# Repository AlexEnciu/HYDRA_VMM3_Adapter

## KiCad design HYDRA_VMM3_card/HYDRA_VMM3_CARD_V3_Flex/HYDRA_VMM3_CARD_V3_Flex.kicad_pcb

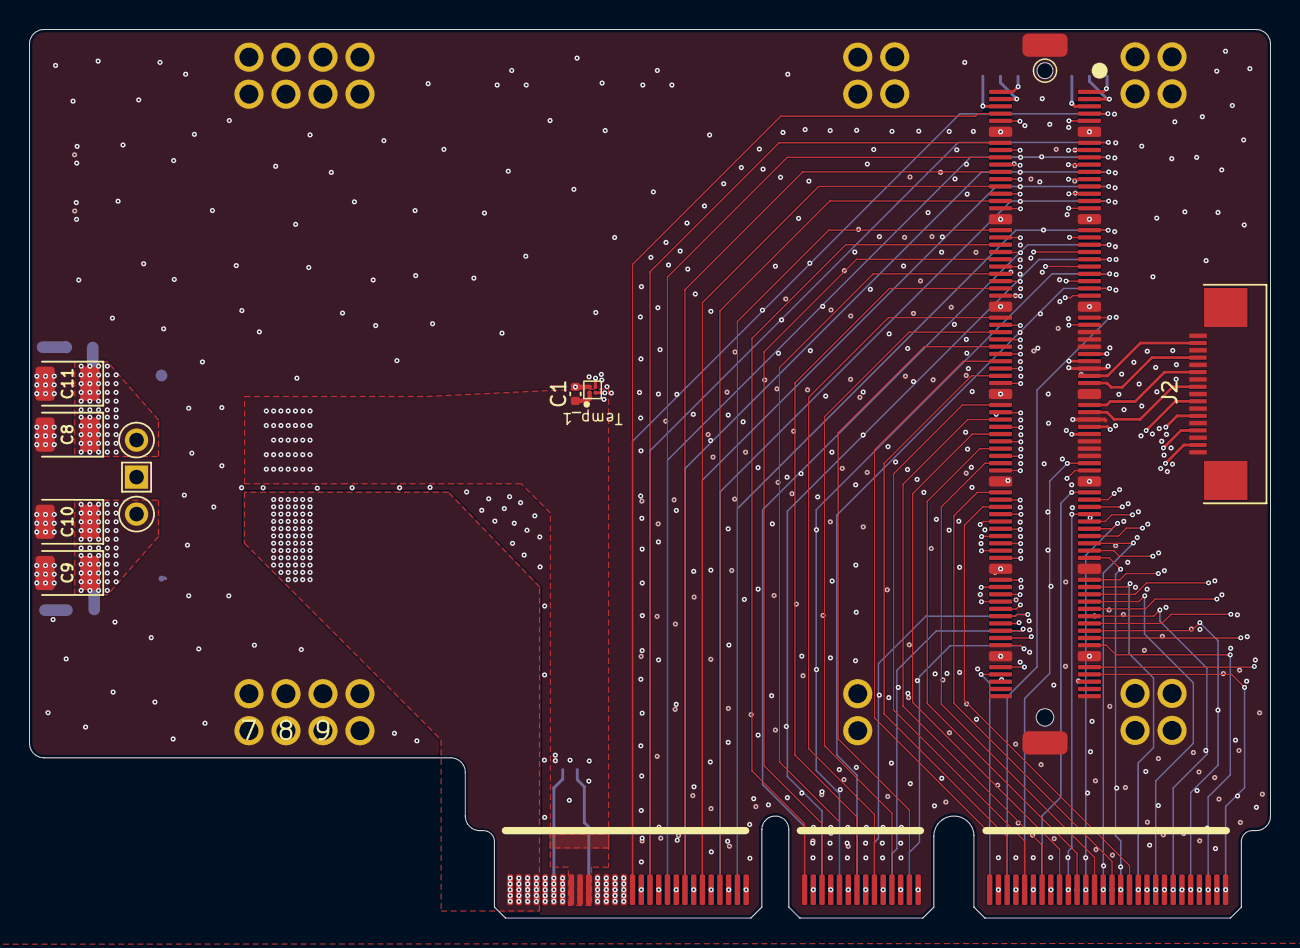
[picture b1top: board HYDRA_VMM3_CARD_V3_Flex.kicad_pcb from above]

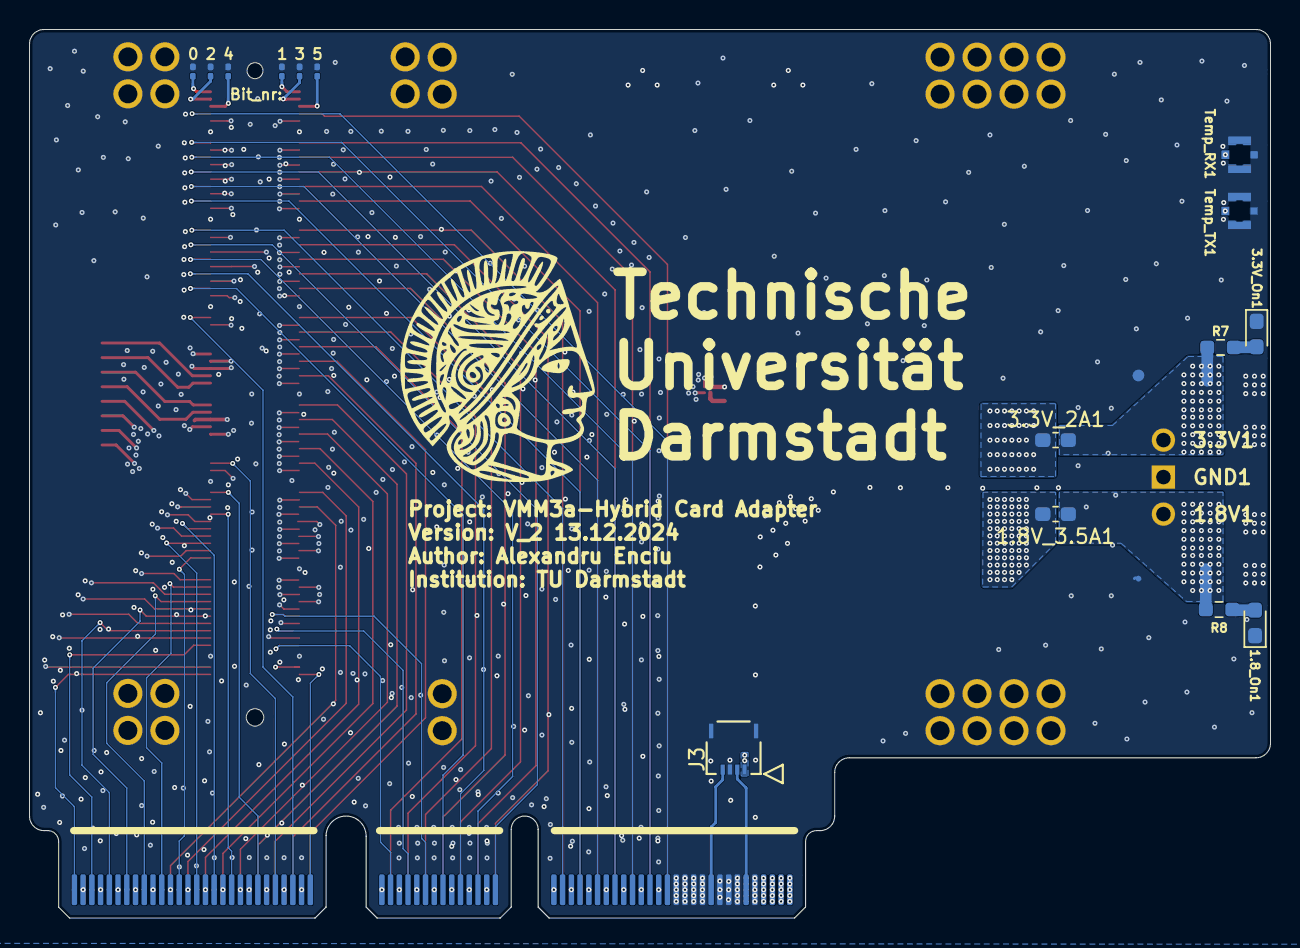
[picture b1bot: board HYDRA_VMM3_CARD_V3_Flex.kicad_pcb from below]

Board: 8 copper layers, 85.2 x 61.0 mm, 43 parts (15 on the bottom side), 136 nets.

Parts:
1, 2, 4, 5, 7, 8, 9, 11, 12, 13, 14, 15, 17, 20, 23, 24: (no value)
1.8V1: 1.8V; TestPoint_Pad_D2.5mm
1.8V_3.5A1: 2.5A; Fuse_0603_1608Metric_Pad1.05x0.95mm_HandSolder
1.8_On1, 3.3V_On1: LED; LED_0603_1608Metric_Pad1.05x0.95mm_HandSolder
3.3V1: 3.3V; TestPoint_Pad_D2.5mm
3.3V_2A1: 2A; Fuse_0603_1608Metric_Pad1.05x0.95mm_HandSolder
C1: 100nF; C_0402_1005Metric
C8, C9, C10, C11: TCJB475M025R0100; CP_EIA-3528-12_Kemet-T
GND1: GND; TestPoint_Pad_2.5x2.5mm
J1: ME1014010101011; Edge-Card-Connector
J2: FPC: 68711714522; 68711714522
J3: FPC_4pin; CON_5034800440_MOL
R1, R2, R3, R4, R5, R6: 10k; R_0201_0603Metric
R7, R8: 1k; R_0603_1608Metric_Pad0.98x0.95mm_HandSolder
Temp_1: TMP104
Temp_RX1: 20449-001E-03; IPEX_20449-001E-03
Temp_TX1: 20449-001E-03; IPEX_20449-001E-03
U1: Hirose-FX10

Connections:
Ch_0: J1.B15, U1.8
Ch_1: J1.A15, U1.7
Ch_2: J1.B16, U1.10
Ch_3: J1.A16, U1.9
Ch_4: J1.B17, U1.12
Ch_5: J1.A17, U1.11
Ch_6: J1.B18, U1.14
Ch_7: J1.A18, U1.13
Ch_8: J1.B19, U1.16
Ch_9: J1.A19, U1.15
Ch_10: J1.B20, U1.18
Ch_11: J1.A20, U1.17
Ch_12: J1.B21, U1.20
Ch_13: J1.A21, U1.19
Ch_14: J1.B22, U1.22
Ch_15: J1.A22, U1.21
Ch_16: J1.B23, U1.24
Ch_17: J1.A23, U1.23
Ch_18: J1.B24, U1.26
Ch_19: J1.A24, U1.25
Ch_20: J1.B25, U1.28
Ch_21: J1.A25, U1.27
Ch_22: J1.B26, U1.30
Ch_23: J1.A26, U1.29
Ch_24: J1.B27, U1.32
Ch_25: J1.A27, U1.31
Ch_26: J1.B28, U1.34
Ch_27: J1.A28, U1.33
Ch_28: J1.B29, U1.36
Ch_29: J1.A29, U1.35
Ch_30: J1.B30, U1.38
Ch_31: J1.A30, U1.37
Ch_32: J1.B31, U1.40
Ch_33: J1.A31, U1.39
Ch_34: J1.B32, U1.42
Ch_35: J1.A32, U1.41
Ch_36: J1.B33, U1.44
Ch_37: J1.A33, U1.43
Ch_38: J1.B34, U1.46
Ch_39: J1.A34, U1.45
Ch_40: J1.B35, U1.48
Ch_41: J1.A35, U1.47
Ch_42: J1.B36, U1.50
Ch_43: J1.A44, U1.49
Ch_44: J1.B37, U1.52
Ch_45: J1.A45, U1.51
Ch_46: J1.B38, U1.54
Ch_47: J1.A46, U1.53
Ch_48: J1.B39, U1.56
Ch_50: J1.B40, U1.58
Ch_52: J1.B41, U1.60
Ch_54: J1.B42, U1.62
Ch_55: J2.8, U1.63
Ch_56: J1.B43, U1.64
Ch_57: J2.6, U1.61
Ch_58: J1.B44, U1.66
Ch_60: J1.B45, U1.68
Ch_61: J2.16, U1.67
Ch_62: J1.B46, U1.70
Ch_63: J2.14, U1.69
Ch_64: J1.B47, U1.72
Ch_65: J2.12, U1.71
Ch_66: J1.B48, U1.74
Ch_67: J2.10, U1.73
Ch_68: J1.B49, U1.76
Ch_70: J1.B50, U1.78
Ch_71: J2.4, U1.77
Ch_72: J1.B51, U1.80
Ch_73: J2.2, U1.79
Ch_74: J1.B52, U1.82
Ch_76: J1.B53, U1.84
Ch_78: J1.B54, U1.86
Ch_80: J1.B55, U1.88
Ch_81: J1.A47, U1.87
Ch_82: J1.B56, U1.90
Ch_83: J1.A48, U1.89
Ch_84: J1.B57, U1.92
Ch_85: J1.A49, U1.91
Ch_86: J1.B58, U1.94
Ch_87: J1.A50, U1.93
Ch_88: J1.B59, U1.96
Ch_89: J1.A51, U1.95
Ch_90: J1.B60, U1.98
Ch_91: J1.A52, U1.97
Ch_92: J1.B61, U1.100
Ch_93: J1.A53, U1.99
Ch_94: J1.B70, U1.102
Ch_95: J1.A54, U1.101
Ch_96: J1.B65, U1.104
Ch_97: J1.A55, U1.103
Ch_98: J1.B69, U1.106
Ch_99: J1.A56, U1.105
Ch_100: J1.B64, U1.108
Ch_101: J1.A57, U1.107
Ch_102: J1.B68, U1.110
Ch_103: J1.A58, U1.109
Ch_104: J1.B67, U1.112
Ch_105: J1.A59, U1.111
Ch_106: J1.B63, U1.114
Ch_107: J1.A60, U1.113
Ch_108: J1.B66, U1.116
Ch_109: J1.A61, U1.115
Ch_110: J1.B62, U1.118
Ch_111: J1.A62, U1.117
Ch_113: J1.A63, U1.119
Ch_114: J1.A36, U1.122
Ch_115: J1.A64, U1.121
Ch_116: J1.A37, U1.124
Ch_117: J1.A65, U1.123
Ch_118: J1.A38, U1.126
Ch_119: J1.A66, U1.125
Ch_120: J1.A39, U1.128
Ch_121: J1.A67, U1.127
Ch_122: J1.A40, U1.130
Ch_123: J1.A68, U1.129
Ch_124: J1.A41, U1.132
Ch_125: J1.A69, U1.131
Ch_126: J1.A42, U1.134
Ch_127: J1.A70, U1.133
GND: 1.1, 1.8_On1.1 (K), 2.1, 3.3V_On1.1 (K), 4.1, 5.1, 7.1, 8.1, 9.1, 11.1, 12.1, 13.1, 14.1, 15.1, 17.1, 20.1, 23.1, 24.1, C1.2, C8.2, C9.2, C10.2, C11.2, GND1.1, J1.A5, J1.A7, J1.A8, J1.A9, J1.A11, J1.A12, J1.A13, J1.A14, J1.B5, J1.B6, J1.B7, J1.B11, J1.B12, J1.B13, J1.B14, J2.1, J2.3, J2.5, J2.7, J2.9, J2.11, J2.13, J2.15, J2.17, J3.3, J3.P1 (Pin_5), J3.P2 (Pin_6), R1.2, R2.2, R3.2, R4.2, R5.2, R6.2, Temp_1.2 (GND), Temp_RX1.2, Temp_RX1.3, Temp_RX1.4, Temp_TX1.2, Temp_TX1.3, Temp_TX1.4, U1.55, U1.57, U1.59, U1.65, U1.75, U1.81, U1.83, U1.85, U1.141 (GND)
Heimtime: J1.A10, J3.4
Master_Trigg: J1.A6, J3.2
unnamed: 1.8_On1.2 (A), R8.2
unnamed: 3.3V_On1.2 (A), R7.2
P1: 3.3V_2A1.1, C1.1, J1.B8, J1.B9, J1.B10, J3.1, Temp_1.1 (V+)
P1_Out: 3.3V1.1, 3.3V_2A1.2, C8.1, C11.1, R7.1
P2: 1.8V_3.5A1.1, J1.A1, J1.A2, J1.A3, J1.A4, J1.B1, J1.B2, J1.B3, J1.B4
P2_Out: 1.8V1.1, 1.8V_3.5A1.2, C9.1, C10.1, R8.1
RX: Temp_1.4 (RX), Temp_RX1.1
TX: Temp_1.3 (TX), Temp_TX1.1
bit_0: R1.1, U1.1
bit_1: R2.1, U1.2
bit_2: R3.1, U1.3
bit_3: R4.1, U1.4
bit_4: R5.1, U1.5
bit_5: R6.1, U1.6

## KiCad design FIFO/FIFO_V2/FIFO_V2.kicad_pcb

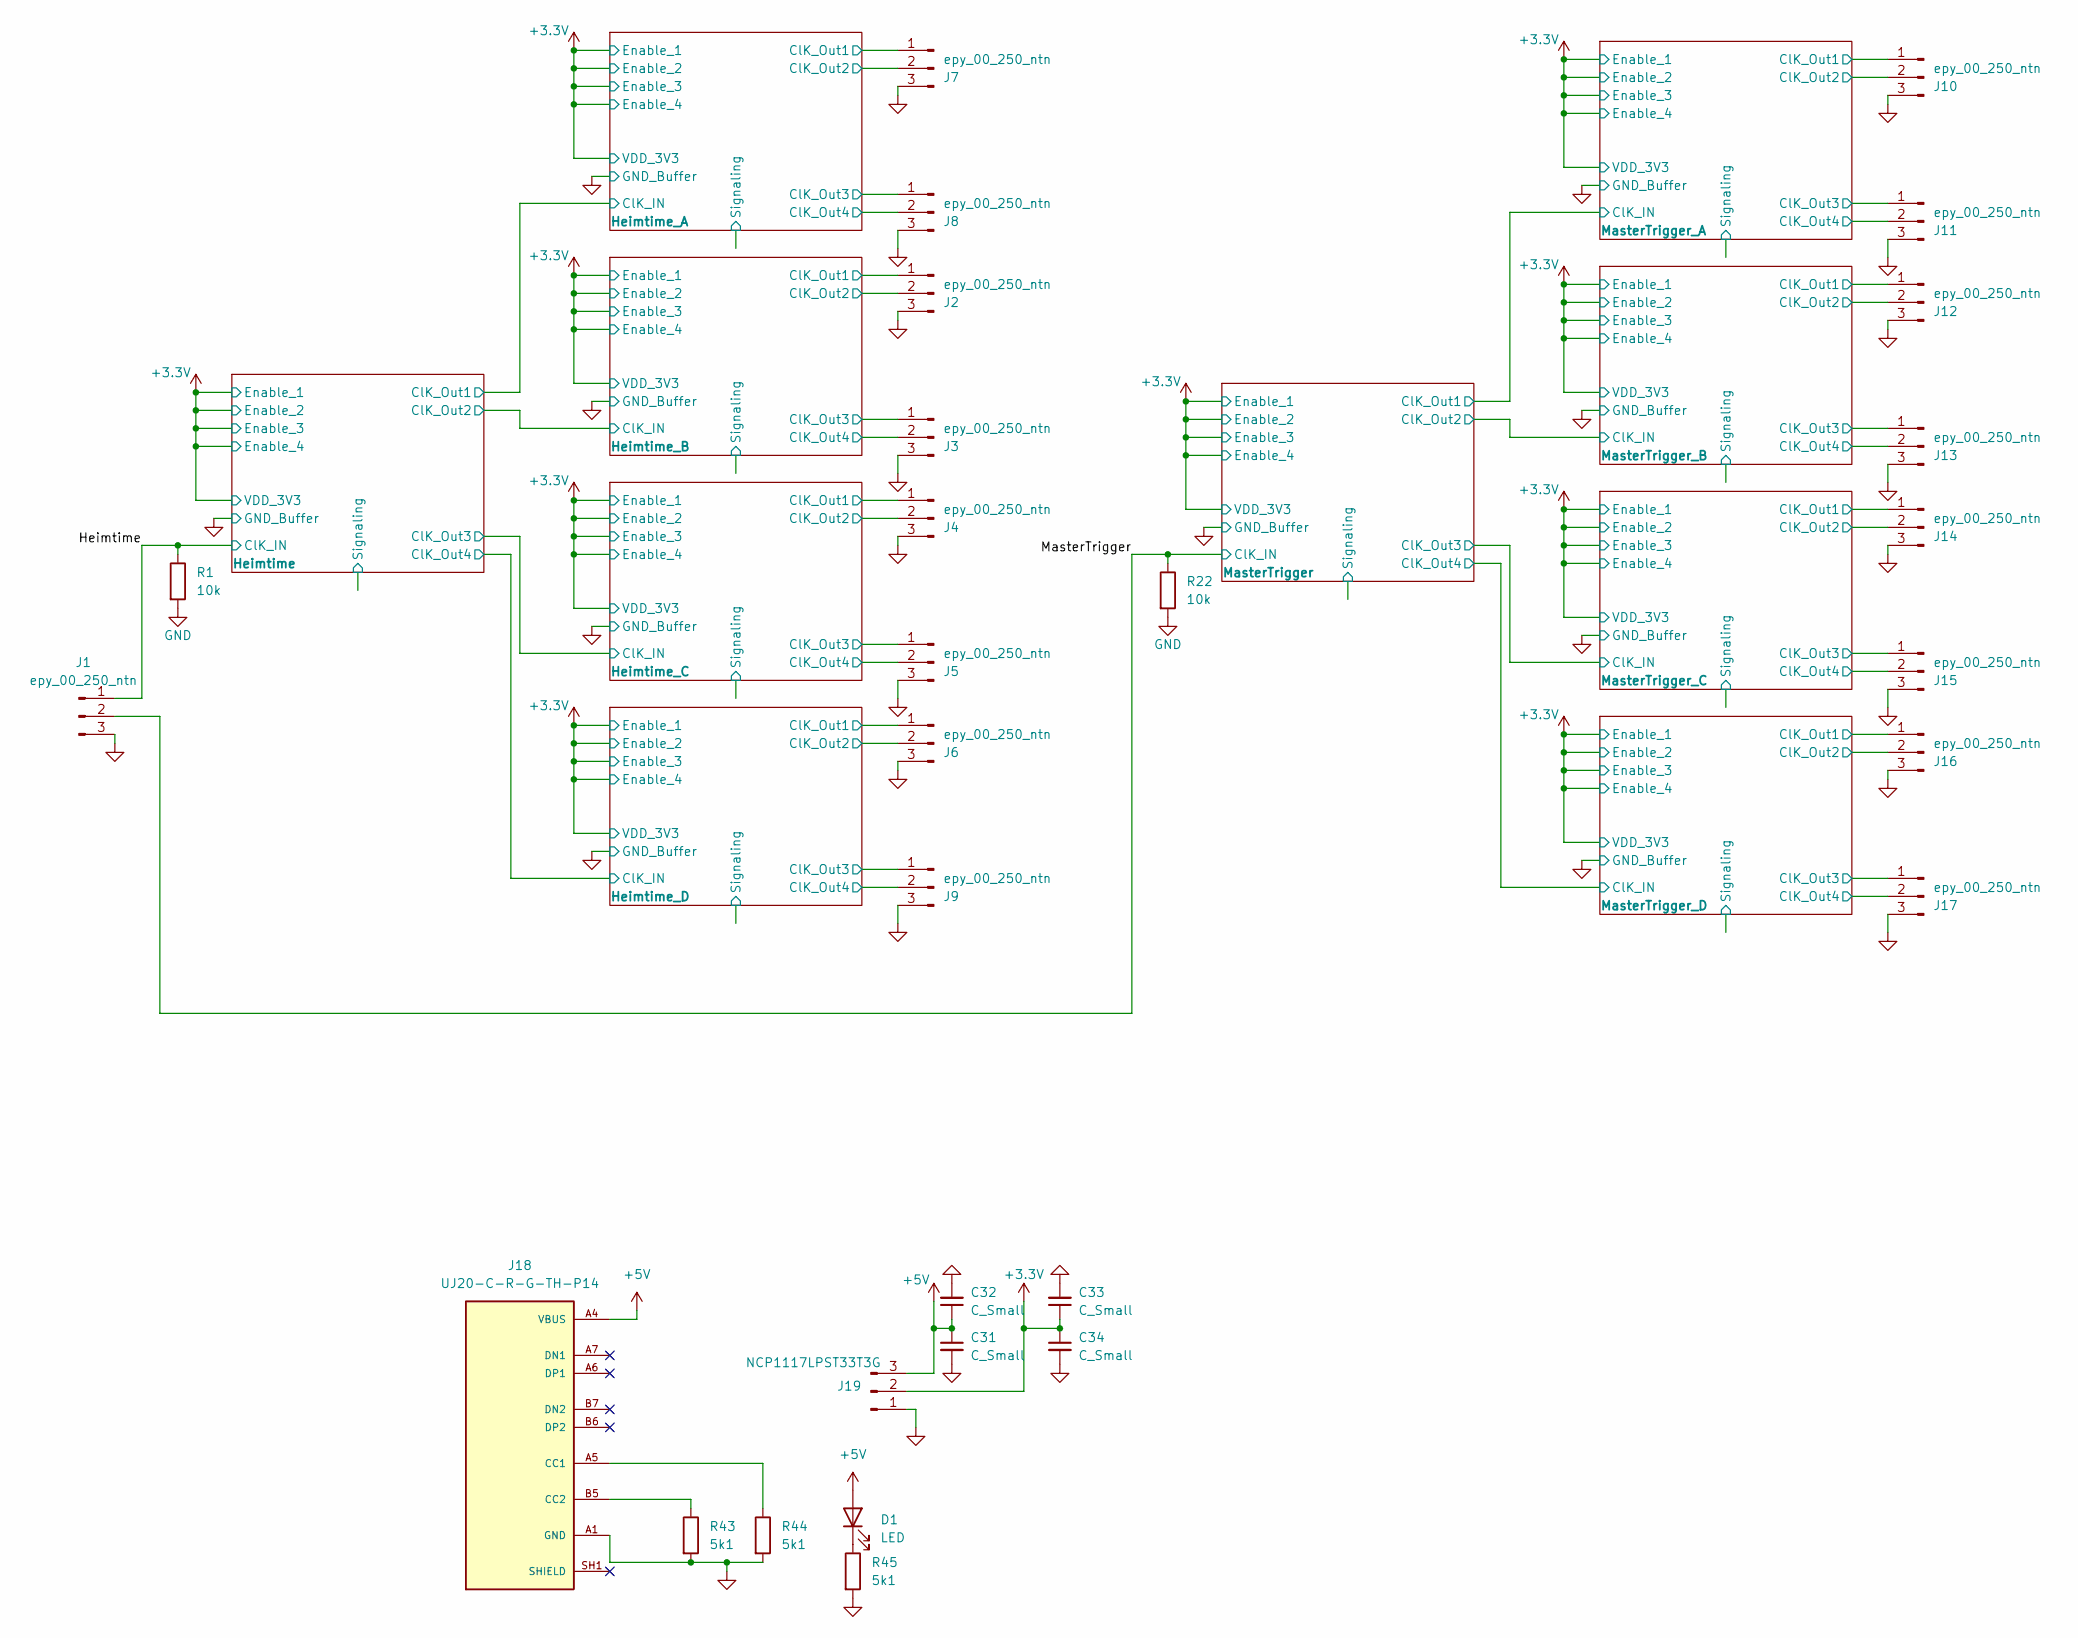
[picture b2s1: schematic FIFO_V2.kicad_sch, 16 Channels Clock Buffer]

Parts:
C31, C32, C33, C34: C_Small; C_0805_2012Metric
D1: LED; LED_D5.0mm
J1, J2, J3, J4, J5, J6, J7, J8, J9, J10, J11, J12, J13, J14, J15, J16, J17: epy_00_250_ntn; LEMO-EPY.00.250.NTN
J18: UJ20-C-R-G-TH-P14; SAMESKY_UJ20-C-R-G-TH-P14; PARTREV 1.0
J19: NCP1117LPST33T3G; SOT-223
R1, R22: 10k; R_0402_1005Metric
R43, R44, R45: 5k1; R_0402_1005Metric

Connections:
+3.3V: C33.1, C34.1, J19.2; also elsewhere on the board
+5V: C31.1, C32.1, D1.2 (A), J18.A4 (VBUS), J18.A9 (VBUS), J18.B4 (VBUS), J18.B9 (VBUS), J19.3
/Heimtime: J1.1, R1.1; also elsewhere on the board
/Heimtime_A/ClK_Out1: J7.1; also elsewhere on the board
/Heimtime_A/ClK_Out2: J7.2; also elsewhere on the board
/Heimtime_A/ClK_Out3: J8.1; also elsewhere on the board
/Heimtime_A/ClK_Out4: J8.2; also elsewhere on the board
/Heimtime_B/ClK_Out1: J2.1; also elsewhere on the board
/Heimtime_B/ClK_Out2: J2.2; also elsewhere on the board
/Heimtime_B/ClK_Out3: J3.1; also elsewhere on the board
/Heimtime_B/ClK_Out4: J3.2; also elsewhere on the board
/Heimtime_C/ClK_Out1: J4.1; also elsewhere on the board
/Heimtime_C/ClK_Out2: J4.2; also elsewhere on the board
/Heimtime_C/ClK_Out3: J5.1; also elsewhere on the board
/Heimtime_C/ClK_Out4: J5.2; also elsewhere on the board
/Heimtime_D/ClK_Out1: J6.1; also elsewhere on the board
/Heimtime_D/ClK_Out2: J6.2; also elsewhere on the board
/Heimtime_D/ClK_Out3: J9.1; also elsewhere on the board
/Heimtime_D/ClK_Out4: J9.2; also elsewhere on the board
/MasterTrigger: J1.2, R22.1; also elsewhere on the board
/MasterTrigger_A/ClK_Out1: J10.1; also elsewhere on the board
/MasterTrigger_A/ClK_Out2: J10.2; also elsewhere on the board
/MasterTrigger_A/ClK_Out3: J11.1; also elsewhere on the board
/MasterTrigger_A/ClK_Out4: J11.2; also elsewhere on the board
/MasterTrigger_B/ClK_Out1: J12.1; also elsewhere on the board
/MasterTrigger_B/ClK_Out2: J12.2; also elsewhere on the board
/MasterTrigger_B/ClK_Out3: J13.1; also elsewhere on the board
/MasterTrigger_B/ClK_Out4: J13.2; also elsewhere on the board
/MasterTrigger_C/ClK_Out1: J14.1; also elsewhere on the board
/MasterTrigger_C/ClK_Out2: J14.2; also elsewhere on the board
/MasterTrigger_C/ClK_Out3: J15.1; also elsewhere on the board
/MasterTrigger_C/ClK_Out4: J15.2; also elsewhere on the board
/MasterTrigger_D/ClK_Out1: J16.1; also elsewhere on the board
/MasterTrigger_D/ClK_Out2: J16.2; also elsewhere on the board
/MasterTrigger_D/ClK_Out3: J17.1; also elsewhere on the board
/MasterTrigger_D/ClK_Out4: J17.2; also elsewhere on the board
GND: C31.2, C32.2, C33.2, C34.2, J1.3, J2.3, J3.3, J4.3, J5.3, J6.3, J7.3, J8.3, J9.3, J10.3, J11.3, J12.3, J13.3, J14.3, J15.3, J16.3, J17.3, J18.A1 (GND), J18.A12 (GND), J18.B1 (GND), J18.B12 (GND), J19.1, R1.2, R22.2, R43.2, R44.2, R45.2; also elsewhere on the board
unnamed: D1.1 (K), R45.1
unnamed: J18.A5 (CC1), R44.1
unnamed: J18.B5 (CC2), R43.1

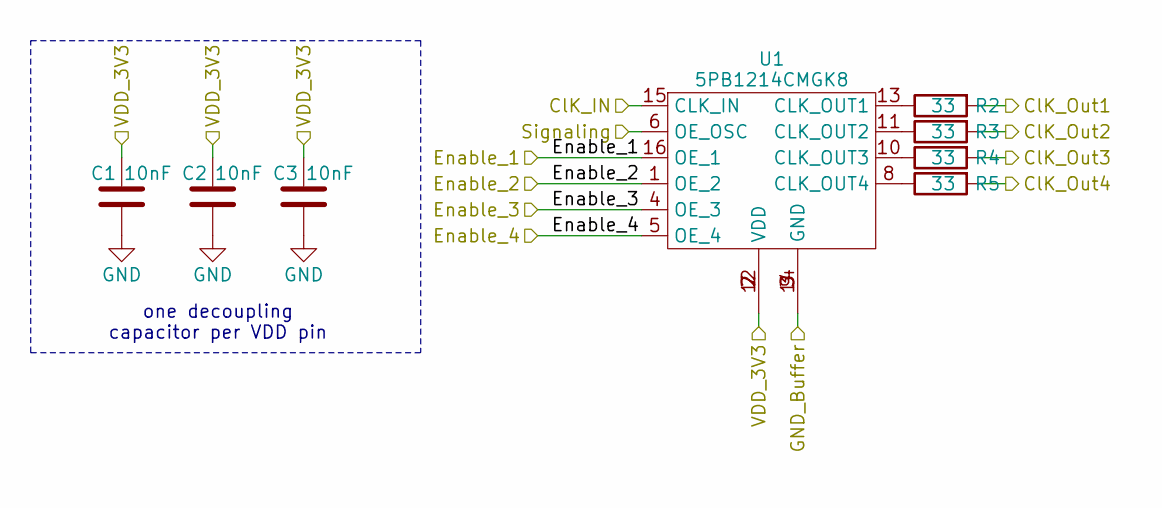
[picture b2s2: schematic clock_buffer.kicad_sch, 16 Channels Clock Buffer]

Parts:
C1, C2, C3: 10nF; C_0402_1005Metric
R2, R3, R4, R5: 33; R_0402_1005Metric
U1: 5PB1214CMGK8

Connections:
+3.3V: C1.2, C2.2, C3.2, U1.1 (OE_2), U1.2 (VDD), U1.4 (OE_3), U1.5 (OE_4), U1.7 (VDD), U1.12 (VDD), U1.16 (OE_1); also elsewhere on the board
/Heimtime: U1.15 (CLK_IN); also elsewhere on the board
/Heimtime/ClK_Out1: R2.2; also elsewhere on the board
/Heimtime/ClK_Out2: R3.2; also elsewhere on the board
/Heimtime/ClK_Out3: R4.2; also elsewhere on the board
/Heimtime/ClK_Out4: R5.2; also elsewhere on the board
/Heimtime/Signaling: U1.6 (OE_OSC)
GND: C1.1, C2.1, C3.1, U1.3 (GND), U1.9 (GND), U1.14 (GND); also elsewhere on the board
unnamed: R2.1, U1.13 (CLK_OUT1)
unnamed: R3.1, U1.11 (CLK_OUT2)
unnamed: R4.1, U1.10 (CLK_OUT3)
unnamed: R5.1, U1.8 (CLK_OUT4)

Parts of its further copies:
C4, C5, C6, C7, C8, C9, C10, C11, C12, C13, C14, C15, C16, C17, C18, C19, C20, C21, C22, C23, C24, C25, C26, C27, C28, C29, C30: 10nF; C_0402_1005Metric
R6, R7, R8, R9, R10, R11, R12, R13, R14, R15, R16, R17, R18, R19, R20, R21, R23, R24, R25, R26, R27, R28, R29, R30, R31, R32, R33, R34, R35, R36, R37, R38, R39, R40, R41, R42: 33; R_0402_1005Metric
U2, U3, U4, U5, U6, U7, U8, U9, U10: 5PB1214CMGK8

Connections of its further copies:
+3.3V: C4.2, C5.2, C6.2, C7.2, C8.2, C9.2, C10.2, C11.2, C12.2, C13.2, C14.2, C15.2, C16.2, C17.2, C18.2, C19.2, C20.2, C21.2, C22.2, C23.2, C24.2, C25.2, C26.2, C27.2, C28.2, C29.2, C30.2, U2.1 (OE_2), U2.2 (VDD), U2.4 (OE_3), U2.5 (OE_4), U2.7 (VDD), U2.12 (VDD), U2.16 (OE_1), U3.1 (OE_2), U3.2 (VDD), U3.4 (OE_3), U3.5 (OE_4), U3.7 (VDD), U3.12 (VDD), U3.16 (OE_1), U4.1 (OE_2), U4.2 (VDD), U4.4 (OE_3), U4.5 (OE_4), U4.7 (VDD), U4.12 (VDD), U4.16 (OE_1), U5.1 (OE_2), U5.2 (VDD), U5.4 (OE_3), U5.5 (OE_4), U5.7 (VDD), U5.12 (VDD), U5.16 (OE_1), U6.1 (OE_2), U6.2 (VDD), U6.4 (OE_3), U6.5 (OE_4), U6.7 (VDD), U6.12 (VDD), U6.16 (OE_1), U7.1 (OE_2), U7.2 (VDD), U7.4 (OE_3), U7.5 (OE_4), U7.7 (VDD), U7.12 (VDD), U7.16 (OE_1), U8.1 (OE_2), U8.2 (VDD), U8.4 (OE_3), U8.5 (OE_4), U8.7 (VDD), U8.12 (VDD), U8.16 (OE_1), U9.1 (OE_2), U9.2 (VDD), U9.4 (OE_3), U9.5 (OE_4), U9.7 (VDD), U9.12 (VDD), U9.16 (OE_1), U10.1 (OE_2), U10.2 (VDD), U10.4 (OE_3), U10.5 (OE_4), U10.7 (VDD), U10.12 (VDD), U10.16 (OE_1); also elsewhere on the board
/Heimtime/ClK_Out1: U2.15 (CLK_IN); also elsewhere on the board
/Heimtime/ClK_Out2: U3.15 (CLK_IN); also elsewhere on the board
/Heimtime/ClK_Out3: U4.15 (CLK_IN); also elsewhere on the board
/Heimtime/ClK_Out4: U5.15 (CLK_IN); also elsewhere on the board
/Heimtime_A/ClK_Out1: R7.2; also elsewhere on the board
/Heimtime_A/ClK_Out2: R8.2; also elsewhere on the board
/Heimtime_A/ClK_Out3: R9.2; also elsewhere on the board
/Heimtime_A/ClK_Out4: R10.2; also elsewhere on the board
/Heimtime_A/Signaling: U2.6 (OE_OSC)
/Heimtime_B/ClK_Out1: R6.2; also elsewhere on the board
/Heimtime_B/ClK_Out2: R11.2; also elsewhere on the board
/Heimtime_B/ClK_Out3: R12.2; also elsewhere on the board
/Heimtime_B/ClK_Out4: R13.2; also elsewhere on the board
/Heimtime_B/Signaling: U3.6 (OE_OSC)
/Heimtime_C/ClK_Out1: R14.2; also elsewhere on the board
/Heimtime_C/ClK_Out2: R15.2; also elsewhere on the board
/Heimtime_C/ClK_Out3: R16.2; also elsewhere on the board
/Heimtime_C/ClK_Out4: R17.2; also elsewhere on the board
/Heimtime_C/Signaling: U4.6 (OE_OSC)
/Heimtime_D/ClK_Out1: R18.2; also elsewhere on the board
/Heimtime_D/ClK_Out2: R19.2; also elsewhere on the board
/Heimtime_D/ClK_Out3: R20.2; also elsewhere on the board
/Heimtime_D/ClK_Out4: R21.2; also elsewhere on the board
/Heimtime_D/Signaling: U5.6 (OE_OSC)
/MasterTrigger: U7.15 (CLK_IN); also elsewhere on the board
/MasterTrigger/ClK_Out1: R27.2, U6.15 (CLK_IN)
/MasterTrigger/ClK_Out2: R28.2, U8.15 (CLK_IN)
/MasterTrigger/ClK_Out3: R29.2, U9.15 (CLK_IN)
/MasterTrigger/ClK_Out4: R30.2, U10.15 (CLK_IN)
/MasterTrigger/Signaling: U7.6 (OE_OSC)
/MasterTrigger_A/ClK_Out1: R23.2; also elsewhere on the board
/MasterTrigger_A/ClK_Out2: R24.2; also elsewhere on the board
/MasterTrigger_A/ClK_Out3: R25.2; also elsewhere on the board
/MasterTrigger_A/ClK_Out4: R26.2; also elsewhere on the board
/MasterTrigger_A/Signaling: U6.6 (OE_OSC)
/MasterTrigger_B/ClK_Out1: R31.2; also elsewhere on the board
/MasterTrigger_B/ClK_Out2: R32.2; also elsewhere on the board
/MasterTrigger_B/ClK_Out3: R33.2; also elsewhere on the board
/MasterTrigger_B/ClK_Out4: R34.2; also elsewhere on the board
/MasterTrigger_B/Signaling: U8.6 (OE_OSC)
/MasterTrigger_C/ClK_Out1: R35.2; also elsewhere on the board
/MasterTrigger_C/ClK_Out2: R36.2; also elsewhere on the board
/MasterTrigger_C/ClK_Out3: R37.2; also elsewhere on the board
/MasterTrigger_C/ClK_Out4: R38.2; also elsewhere on the board
/MasterTrigger_C/Signaling: U9.6 (OE_OSC)
/MasterTrigger_D/ClK_Out1: R39.2; also elsewhere on the board
/MasterTrigger_D/ClK_Out2: R40.2; also elsewhere on the board
/MasterTrigger_D/ClK_Out3: R41.2; also elsewhere on the board
/MasterTrigger_D/ClK_Out4: R42.2; also elsewhere on the board
/MasterTrigger_D/Signaling: U10.6 (OE_OSC)
GND: C4.1, C5.1, C6.1, C7.1, C8.1, C9.1, C10.1, C11.1, C12.1, C13.1, C14.1, C15.1, C16.1, C17.1, C18.1, C19.1, C20.1, C21.1, C22.1, C23.1, C24.1, C25.1, C26.1, C27.1, C28.1, C29.1, C30.1, U2.3 (GND), U2.9 (GND), U2.14 (GND), U3.3 (GND), U3.9 (GND), U3.14 (GND), U4.3 (GND), U4.9 (GND), U4.14 (GND), U5.3 (GND), U5.9 (GND), U5.14 (GND), U6.3 (GND), U6.9 (GND), U6.14 (GND), U7.3 (GND), U7.9 (GND), U7.14 (GND), U8.3 (GND), U8.9 (GND), U8.14 (GND), U9.3 (GND), U9.9 (GND), U9.14 (GND), U10.3 (GND), U10.9 (GND), U10.14 (GND); also elsewhere on the board
unnamed: R7.1, U2.13 (CLK_OUT1)
unnamed: R8.1, U2.11 (CLK_OUT2)
unnamed: R9.1, U2.10 (CLK_OUT3)
unnamed: R10.1, U2.8 (CLK_OUT4)
unnamed: R6.1, U3.13 (CLK_OUT1)
unnamed: R11.1, U3.11 (CLK_OUT2)
unnamed: R12.1, U3.10 (CLK_OUT3)
unnamed: R13.1, U3.8 (CLK_OUT4)
unnamed: R14.1, U4.13 (CLK_OUT1)
unnamed: R15.1, U4.11 (CLK_OUT2)
unnamed: R16.1, U4.10 (CLK_OUT3)
unnamed: R17.1, U4.8 (CLK_OUT4)
unnamed: R18.1, U5.13 (CLK_OUT1)
unnamed: R19.1, U5.11 (CLK_OUT2)
unnamed: R20.1, U5.10 (CLK_OUT3)
unnamed: R21.1, U5.8 (CLK_OUT4)
unnamed: R23.1, U6.13 (CLK_OUT1)
unnamed: R24.1, U6.11 (CLK_OUT2)
unnamed: R25.1, U6.10 (CLK_OUT3)
unnamed: R26.1, U6.8 (CLK_OUT4)
unnamed: R27.1, U7.13 (CLK_OUT1)
unnamed: R28.1, U7.11 (CLK_OUT2)
unnamed: R29.1, U7.10 (CLK_OUT3)
unnamed: R30.1, U7.8 (CLK_OUT4)
unnamed: R31.1, U8.13 (CLK_OUT1)
unnamed: R32.1, U8.11 (CLK_OUT2)
unnamed: R33.1, U8.10 (CLK_OUT3)
unnamed: R34.1, U8.8 (CLK_OUT4)
unnamed: R35.1, U9.13 (CLK_OUT1)
unnamed: R36.1, U9.11 (CLK_OUT2)
unnamed: R37.1, U9.10 (CLK_OUT3)
unnamed: R38.1, U9.8 (CLK_OUT4)
unnamed: R39.1, U10.13 (CLK_OUT1)
unnamed: R40.1, U10.11 (CLK_OUT2)
unnamed: R41.1, U10.10 (CLK_OUT3)
unnamed: R42.1, U10.8 (CLK_OUT4)

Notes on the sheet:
one decoupling capacitor per VDD pin

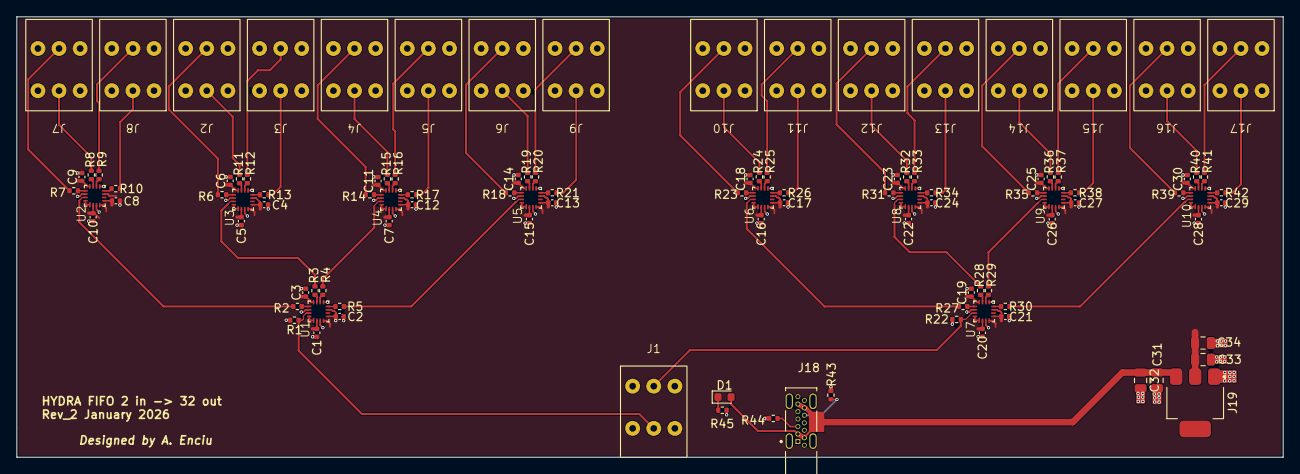
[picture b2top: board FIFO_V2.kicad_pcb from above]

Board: 2 copper layers, 152.4 x 53.0 mm, 109 parts (0 on the bottom side), 88 nets.

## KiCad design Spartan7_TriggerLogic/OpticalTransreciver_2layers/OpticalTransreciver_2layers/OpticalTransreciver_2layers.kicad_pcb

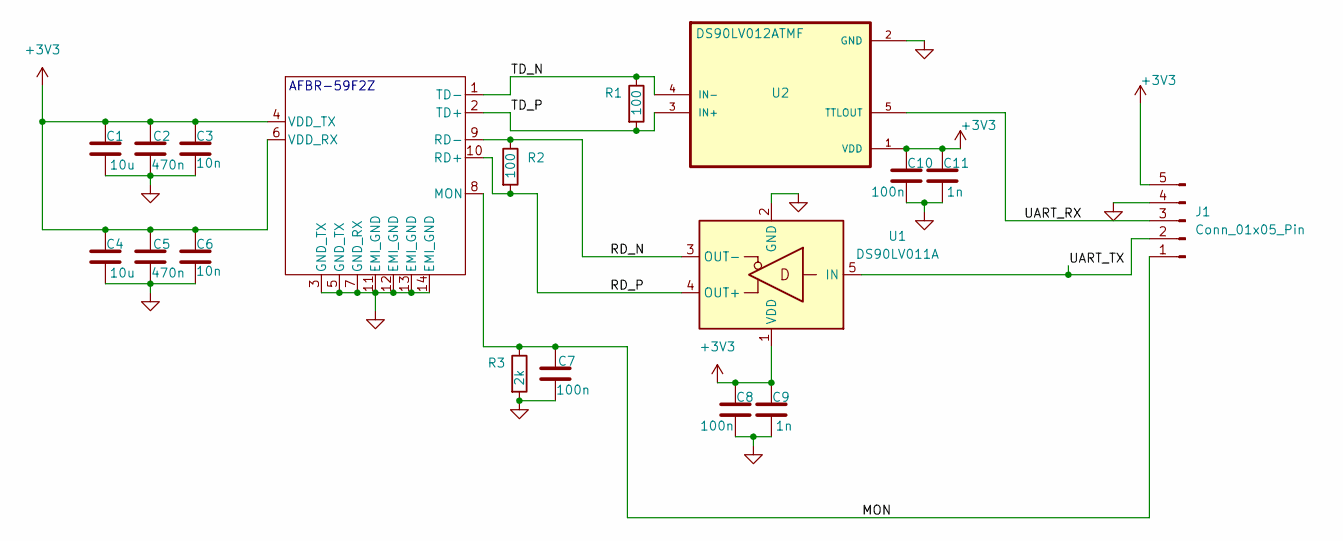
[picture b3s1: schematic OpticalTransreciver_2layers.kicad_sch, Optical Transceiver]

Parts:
C1, C4: 10u; C_0603_1608Metric
C2, C5: 470n; C_0603_1608Metric
C3, C6: 10n; C_0603_1608Metric
C7, C8, C10: 100n; C_0603_1608Metric
C9, C11: 1n; C_0603_1608Metric
Conn1: AFBR-59F2Z; AFBR-5803ZTZ_AVA
J1: Conn_01x05_Pin; PinHeader_1x05_P2.54mm_Vertical
R1, R2: 100; R_0603_1608Metric
R3: 2k; R_0603_1608Metric
U1: DS90LV011A; SOT-23-5
U2: DS90LV012ATMF; SOT-23-5

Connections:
+3V3: C1.1, C2.1, C3.1, C4.1, C5.1, C6.1, C8.1, C9.1, C10.1, C11.1, Conn1.4 (VDD_TX), Conn1.6 (VDD_RX), J1.5, U1.1 (VDD), U2.1 (VDD)
/MON: C7.1, Conn1.8 (MON), J1.1, R3.1
/RD_N: Conn1.9 (RD-), R2.1, U1.3 (OUT-)
/RD_P: Conn1.10 (RD+), R2.2, U1.4 (OUT+)
/TD_N: Conn1.1 (TD-), R1.1, U2.4 (IN-)
/TD_P: Conn1.2 (TD+), R1.2, U2.3 (IN+)
/UART_RX: J1.3, U2.5 (TTLOUT)
/UART_TX: J1.2, U1.5 (IN)
GND: C1.2, C2.2, C3.2, C4.2, C5.2, C6.2, C7.2, C8.2, C9.2, C10.2, C11.2, Conn1.3 (GND_TX), Conn1.5 (GND_TX), Conn1.7 (GND_RX), Conn1.11 (EMI_GND), Conn1.12 (EMI_GND), Conn1.13 (EMI_GND), Conn1.14 (EMI_GND), J1.4, R3.2, U1.2 (GND), U2.2 (GND)

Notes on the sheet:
AFBR-59F2Z

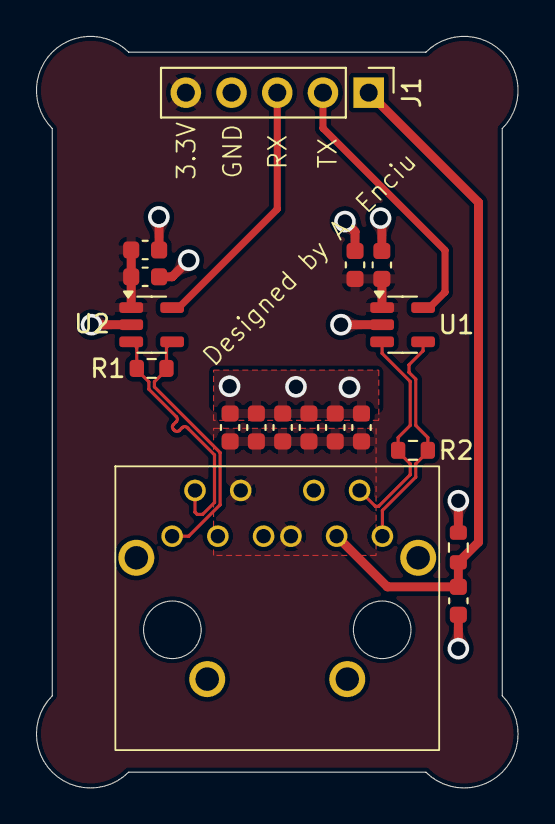
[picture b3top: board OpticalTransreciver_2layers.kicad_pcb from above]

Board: 2 copper layers, 26.8 x 41.8 mm, 18 parts (0 on the bottom side), 9 nets.

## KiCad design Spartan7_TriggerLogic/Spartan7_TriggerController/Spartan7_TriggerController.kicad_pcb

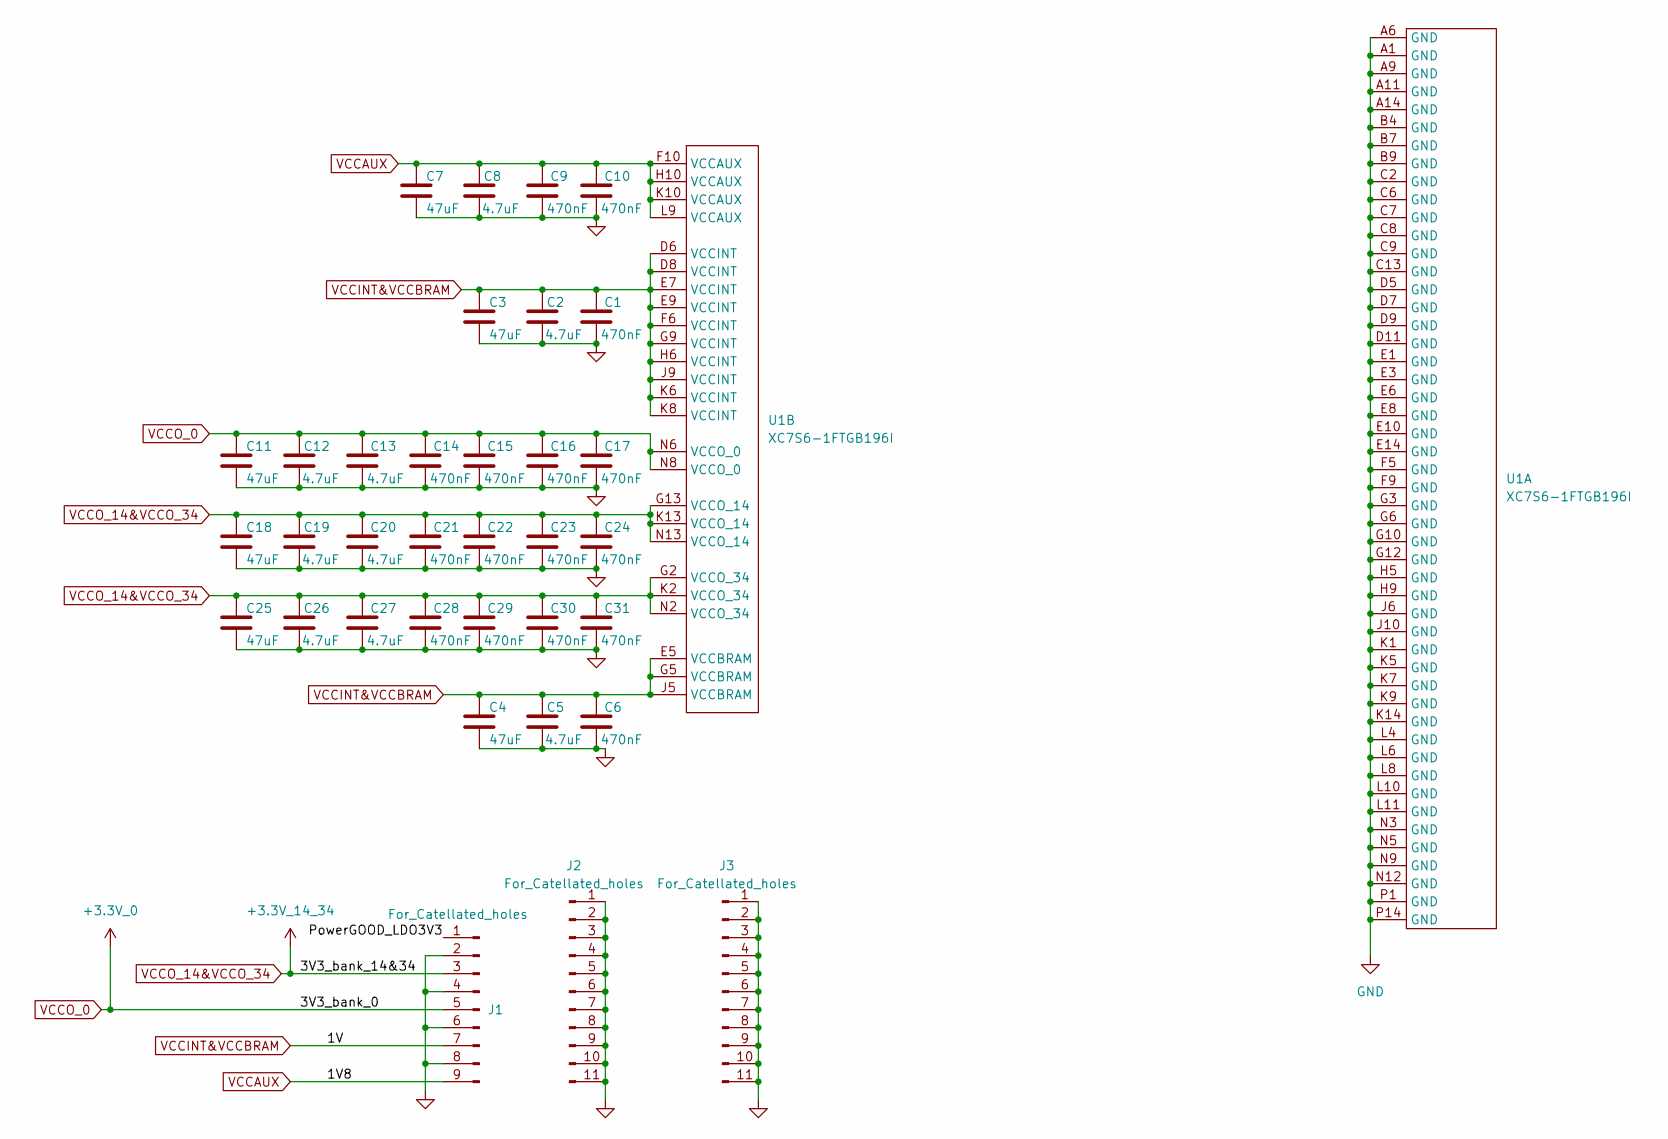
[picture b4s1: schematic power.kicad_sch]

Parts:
C1, C6, C9, C10, C14, C15, C16, C17, C21, C22, C23, C24, C28, C29, C30, C31: 470nF; C_0402_1005Metric
C2, C5, C8, C12, C13, C19, C20, C26, C27: 4.7uF; C_0603_1608Metric
C3, C4, C7, C11, C18, C25: 47uF; C_1210_3225Metric
J1: For_Catellated_holes; PinHeader_1x09_P2.54mm_Vertical
J2, J3: For_Catellated_holes; PinHeader_1x11_P2.54mm_Vertical
U1: XC7S6-1FTGB196I; BGA196C100P14X14_1500X1500X155N

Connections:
/Power/PowerGOOD_LDO3V3: J1.1
GND: C1.2, C2.2, C3.2, C4.2, C5.2, C6.2, C7.2, C8.2, C9.2, C10.2, C11.2, C12.2, C13.2, C14.2, C15.2, C16.2, C17.2, C18.2, C19.2, C20.2, C21.2, C22.2, C23.2, C24.2, C25.2, C26.2, C27.2, C28.2, C29.2, C30.2, C31.2, J1.2, J1.4, J1.6, J1.8, J2.1, J2.2, J2.3, J2.4, J2.5, J2.6, J2.7, J2.8, J2.9, J2.10, J2.11, J3.1, J3.2, J3.3, J3.4, J3.5, J3.6, J3.7, J3.8, J3.9, J3.10, J3.11, U1.A1 (GND), U1.A6 (GND), U1.A9 (GND), U1.A11 (GND), U1.A14 (GND), U1.B4 (GND), U1.B7 (GND), U1.B9 (GND), U1.C2 (GND), U1.C6 (GND), U1.C7 (GND), U1.C8 (GND), U1.C9 (GND), U1.C13 (GND), U1.D5 (GND), U1.D7 (GND), U1.D9 (GND), U1.D11 (GND), U1.E1 (GND), U1.E3 (GND), U1.E6 (GND), U1.E8 (GND), U1.E10 (GND), U1.E14 (GND), U1.F5 (GND), U1.F9 (GND), U1.G3 (GND), U1.G6 (GND), U1.G10 (GND), U1.G12 (GND), U1.H5 (GND), U1.H9 (GND), U1.J6 (GND), U1.J10 (GND), U1.K1 (GND), U1.K5 (GND), U1.K7 (GND), U1.K9 (GND), U1.K14 (GND), U1.L4 (GND), U1.L6 (GND), U1.L8 (GND), U1.L10 (GND), U1.L11 (GND), U1.N3 (GND), U1.N5 (GND), U1.N9 (GND), U1.N12 (GND), U1.P1 (GND), U1.P14 (GND); also elsewhere on the board
VCCAUX: C7.1, C8.1, C9.1, C10.1, J1.9, U1.F10 (VCCAUX), U1.H10 (VCCAUX), U1.K10 (VCCAUX), U1.L9 (VCCAUX)
VCCINT&VCCBRAM: C1.1, C2.1, C3.1, C4.1, C5.1, C6.1, J1.7, U1.D6 (VCCINT), U1.D8 (VCCINT), U1.E5 (VCCBRAM), U1.E7 (VCCINT), U1.E9 (VCCINT), U1.F6 (VCCINT), U1.G5 (VCCBRAM), U1.G9 (VCCINT), U1.H6 (VCCINT), U1.J5 (VCCBRAM), U1.J9 (VCCINT), U1.K6 (VCCINT), U1.K8 (VCCINT)
VCCO_0: C11.1, C12.1, C13.1, C14.1, C15.1, C16.1, C17.1, J1.5, U1.N6 (VCCO_0), U1.N8 (VCCO_0)
VCCO_14&VCCO_34: C18.1, C19.1, C20.1, C21.1, C22.1, C23.1, C24.1, C25.1, C26.1, C27.1, C28.1, C29.1, C30.1, C31.1, J1.3, U1.G2 (VCCO_34), U1.G13 (VCCO_14), U1.K2 (VCCO_34), U1.K13 (VCCO_14), U1.N2 (VCCO_34), U1.N13 (VCCO_14); also elsewhere on the board
